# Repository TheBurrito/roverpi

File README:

RoPi - Robotics for the Raspberry Pi
https://github.com/TheBurrito/ropi

This repository contains all of the source code for both the Raspberry Pi and
the ATmega2560 on the RoPi expansion board.

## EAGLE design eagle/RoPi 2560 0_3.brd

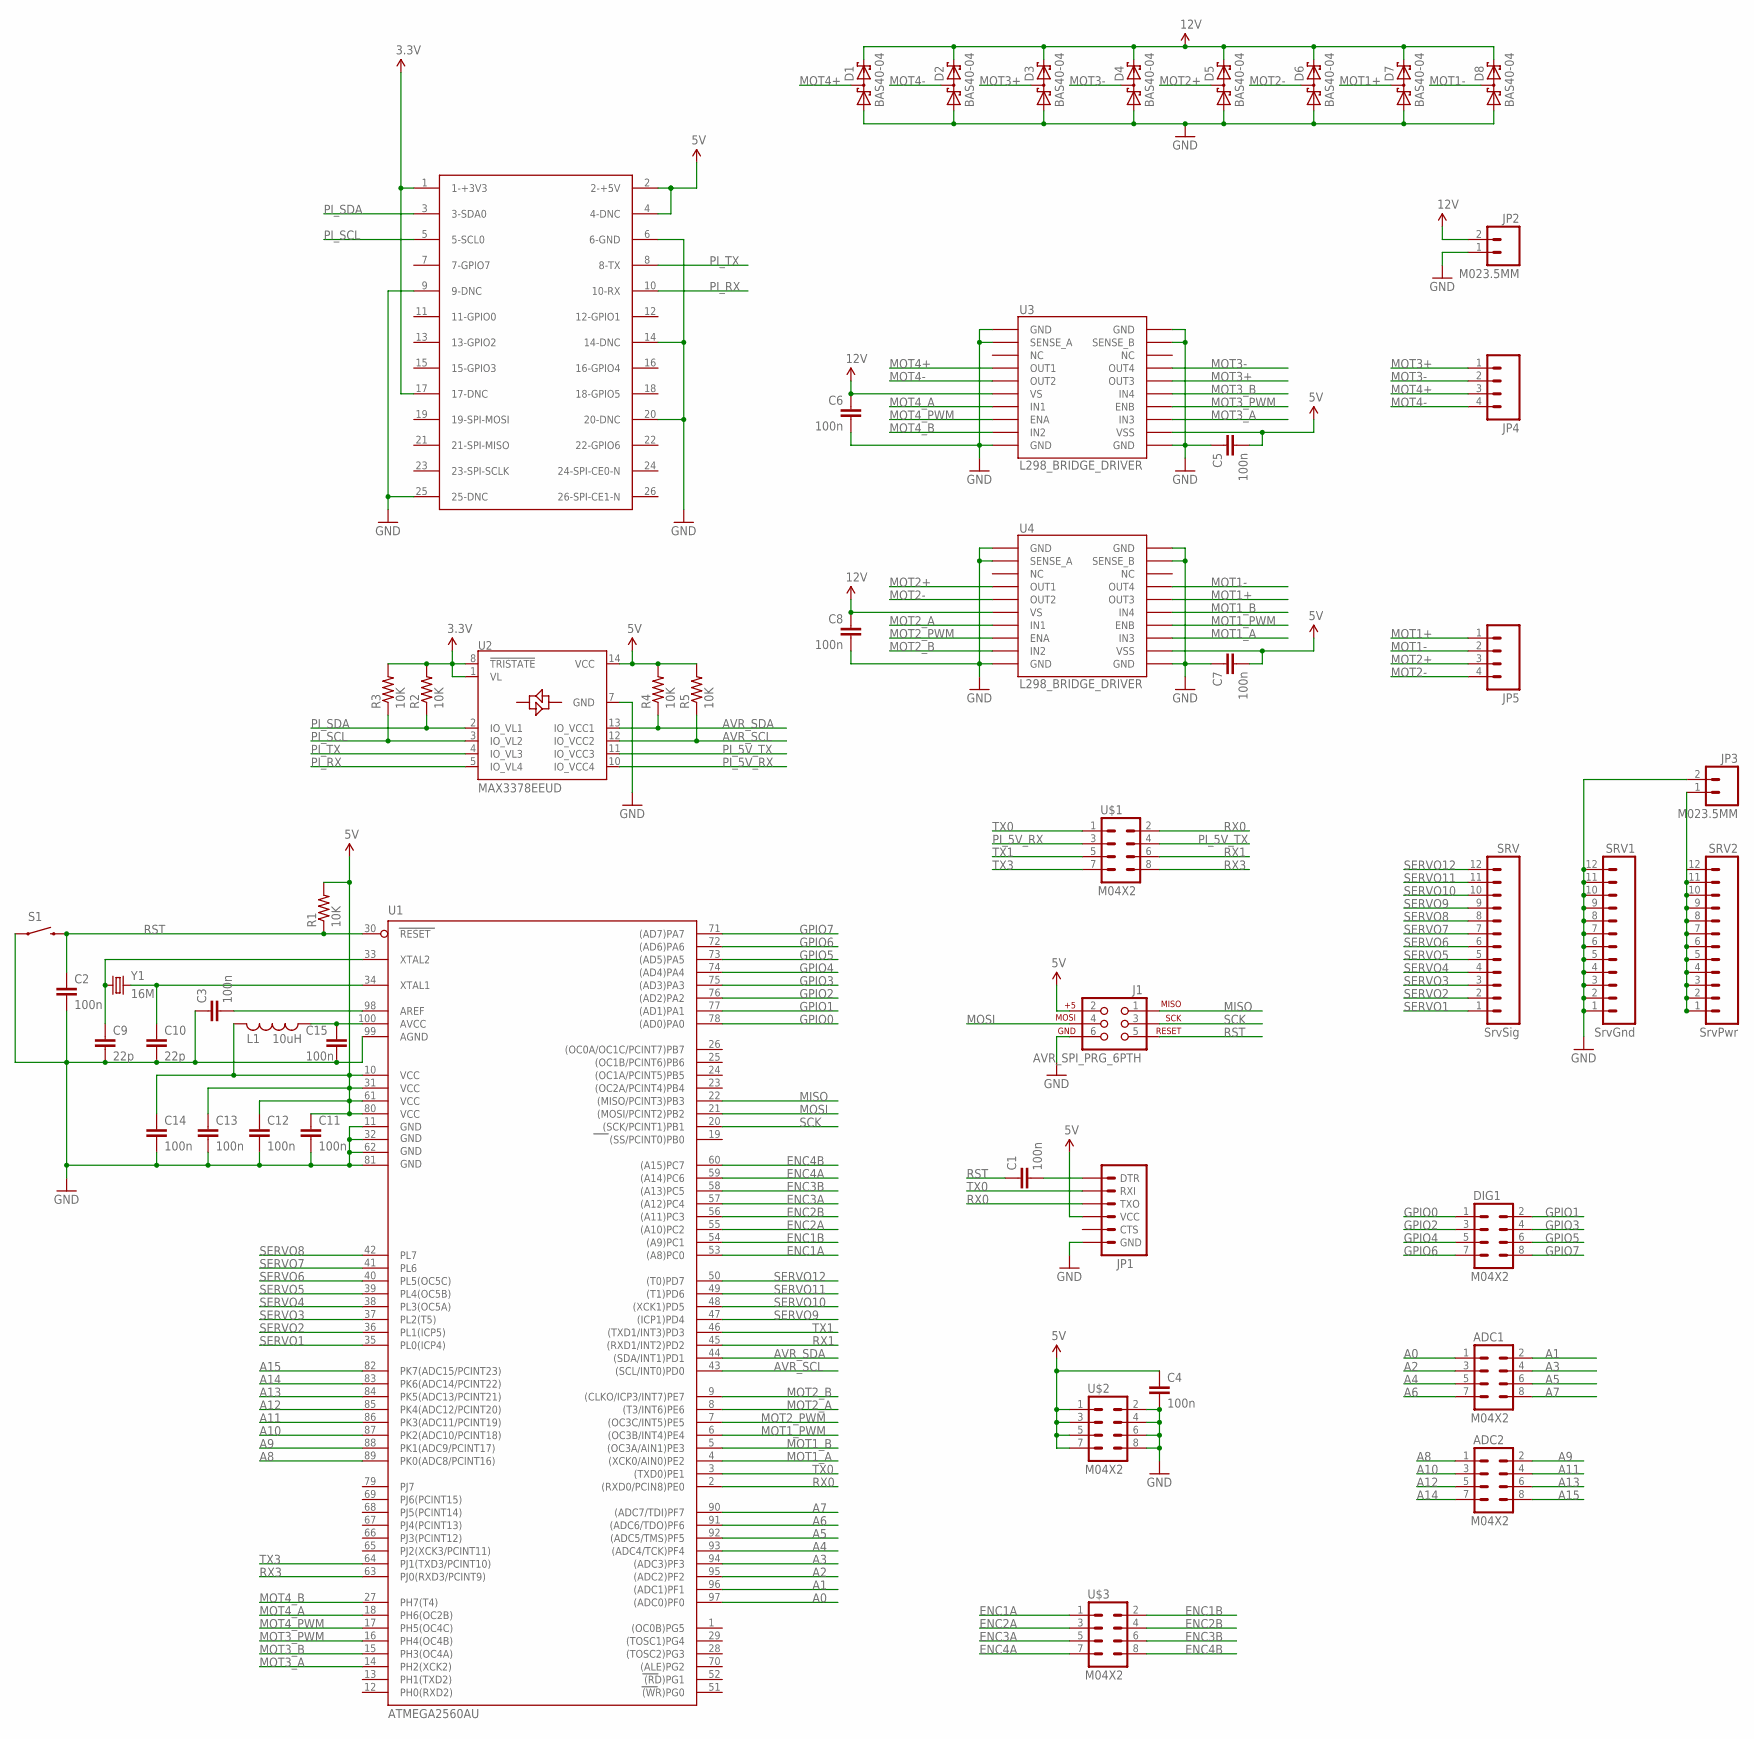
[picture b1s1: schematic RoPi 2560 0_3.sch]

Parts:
ADC1, ADC2: M04X2; 2X4
C1, C2, C3, C4, C5, C6, C7, C8, C11, C12, C13, C14, C15: 100n; 0603-CAP
C9, C10: 22p; 0603-CAP
D1, D2, D3, D4, D5, D6, D7, D8: BAS40-04; SOT23
DIG1: M04X2; 2X4
J1: AVR_SPI_PRG_6PTH; 2X3
JP1: ARDUINO_SERIAL_PROGRAMSMD; 1X06-SMD
JP2, JP3: M023.5MM; SCREWTERMINAL-3.5MM-2
JP4, JP5: M04SCREW; SCREWTERMINAL-3.5MM-4
L1: 10uH; R0603
PI: RASPBERRY-PI
R1, R2, R3, R4, R5: 10K; 0603-RES
S1: SWITCH-MOMENTARY-2SMD-4; TACTILE_SWITCH_TALL
SRV: SrvSig; 1X12
SRV1: SrvGnd; 1X12
SRV2: SrvPwr; 1X12
U1: ATMEGA2560AU; TQFP100
U2: MAX3378EEUD; TSSOP14
U3, U4: L298_BRIDGE_DRIVER; POWERSO20
U$1, U$2, U$3: M04X2; 2X4
Y1: 16M; HC49UP

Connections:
3.3V: PI.1 (1-+3V3), PI.17 (17-DNC), R2.2, R3.2, U2.1 (VL), U2.8 (!TRISTATE)
5V: C4.1, C5.2, C7.2, C11.1, C12.1, C13.1, C14.1, J1.2, JP1.4 (VCC), L1.2, PI.2 (2-+5V), PI.4 (4-DNC), R1.2, R4.2, R5.2, U1.10 (VCC), U1.31 (VCC1), U1.61 (VCC2), U1.80 (VCC3), U2.14 (VCC), U3.12 (VSS), U4.12 (VSS), U$2.1, U$2.3, U$2.5, U$2.7
A0: ADC1.1, U1.97 ((ADC0)PF0)
A1: ADC1.2, U1.96 ((ADC1)PF1)
A2: ADC1.3, U1.95 ((ADC2)PF2)
A3: ADC1.4, U1.94 ((ADC3)PF3)
A4: ADC1.5, U1.93 ((ADC4/TCK)PF4)
A5: ADC1.6, U1.92 ((ADC5/TMS)PF5)
A6: ADC1.7, U1.91 ((ADC6/TDO)PF6)
A7: ADC1.8, U1.90 ((ADC7/TDI)PF7)
A8: ADC2.1, U1.89 (PK0(ADC8/PCINT16))
A9: ADC2.2, U1.88 (PK1(ADC9/PCINT17))
A10: ADC2.3, U1.87 (PK2(ADC10/PCINT18))
A11: ADC2.4, U1.86 (PK3(ADC11/PCINT19))
A12: ADC2.5, U1.85 (PK4(ADC12/PCINT20))
A13: ADC2.6, U1.84 (PK5(ADC13/PCINT21))
A14: ADC2.7, U1.83 (PK6(ADC14/PCINT22))
A15: ADC2.8, U1.82 (PK7(ADC15/PCINT23))
AREF: C3.2, U1.98 (AREF)
AVR_SCL: R5.1, U1.43 ((SCL/INT0)PD0), U2.12 (IO_VCC2)
AVR_SDA: R4.1, U1.44 ((SDA/INT1)PD1), U2.13 (IO_VCC1)
DTR: C1.2, JP1.1 (DTR)
ENC1A: U1.53 ((A8)PC0), U$3.1
ENC1B: U1.54 ((A9)PC1), U$3.2
ENC2A: U1.55 ((A10)PC2), U$3.3
ENC2B: U1.56 ((A11)PC3), U$3.4
ENC3A: U1.57 ((A12)PC4), U$3.5
ENC3B: U1.58 ((A13)PC5), U$3.6
ENC4A: U1.59 ((A14)PC6), U$3.7
ENC4B: U1.60 ((A15)PC7), U$3.8
GND: C2.2, C3.1, C4.2, C5.1, C6.2, C7.1, C8.2, C9.2, C10.2, C11.2, C12.2, C13.2, C14.2, C15.2, D1.1 (A1), D2.1 (A1), D3.1 (A1), D4.1 (A1), D5.1 (A1), D6.1 (A1), D7.1 (A1), D8.1 (A1), J1.6, JP1.6 (GND), JP2.1, JP3.2, PI.6 (6-GND), PI.9 (9-DNC), PI.14 (14-DNC), PI.20 (20-DNC), PI.25 (25-DNC), S1.A2 (1), SRV1.1, SRV1.2, SRV1.3, SRV1.4, SRV1.5, SRV1.6, SRV1.7, SRV1.8, SRV1.9, SRV1.10, SRV1.11, SRV1.12, U1.11 (GND), U1.32 (GND1), U1.62 (GND2), U1.81 (GND3), U1.99 (AGND), U2.7 (GND), U3.1 (GND), U3.2 (SENSE_A), U3.10 (GND), U3.11 (GND), U3.19 (SENSE_B), U3.20 (GND), U4.1 (GND), U4.2 (SENSE_A), U4.10 (GND), U4.11 (GND), U4.19 (SENSE_B), U4.20 (GND), U$2.2, U$2.4, U$2.6, U$2.8
GPIO0: DIG1.1, U1.78 ((AD0)PA0)
GPIO1: DIG1.2, U1.77 ((AD1)PA1)
GPIO2: DIG1.3, U1.76 ((AD2)PA2)
GPIO3: DIG1.4, U1.75 ((AD3)PA3)
GPIO4: DIG1.5, U1.74 ((AD4)PA4)
GPIO5: DIG1.6, U1.73 ((AD5)PA5)
GPIO6: DIG1.7, U1.72 ((AD6)PA6)
GPIO7: DIG1.8, U1.71 ((AD7)PA7)
MISO: J1.1, U1.22 ((MISO/PCINT3)PB3)
MOSI: J1.4, U1.21 ((MOSI/PCINT2)PB2)
MOT1+: D7.3 (C1A2), JP5.1, U4.16 (OUT3)
MOT1-: D8.3 (C1A2), JP5.2, U4.17 (OUT4)
MOT1_A: U1.4 ((XCK0/AIN0)PE2), U4.13 (IN3)
MOT1_B: U1.5 ((OC3A/AIN1)PE3), U4.15 (IN4)
MOT1_PWM: U1.6 ((OC3B/INT4)PE4), U4.14 (ENB)
MOT2+: D5.3 (C1A2), JP5.3, U4.4 (OUT1)
MOT2-: D6.3 (C1A2), JP5.4, U4.5 (OUT2)
MOT2_A: U1.8 ((T3/INT6)PE6), U4.7 (IN1)
MOT2_B: U1.9 ((CLKO/ICP3/INT7)PE7), U4.9 (IN2)
MOT2_PWM: U1.7 ((OC3C/INT5)PE5), U4.8 (ENA)
MOT3+: D3.3 (C1A2), JP4.1, U3.16 (OUT3)
MOT3-: D4.3 (C1A2), JP4.2, U3.17 (OUT4)
MOT3_A: U1.14 (PH2(XCK2)), U3.13 (IN3)
MOT3_B: U1.15 (PH3(OC4A)), U3.15 (IN4)
MOT3_PWM: U1.16 (PH4(OC4B)), U3.14 (ENB)
MOT4+: D1.3 (C1A2), JP4.3, U3.4 (OUT1)
MOT4-: D2.3 (C1A2), JP4.4, U3.5 (OUT2)
MOT4_A: U1.18 (PH6(OC2B)), U3.7 (IN1)
MOT4_B: U1.27 (PH7(T4)), U3.9 (IN2)
MOT4_PWM: U1.17 (PH5(OC4C)), U3.8 (ENA)
unnamed: JP3.1, SRV2.1, SRV2.2, SRV2.3, SRV2.4, SRV2.5, SRV2.6, SRV2.7, SRV2.8, SRV2.9, SRV2.10, SRV2.11, SRV2.12
unnamed: C15.1, L1.1, U1.100 (AVCC)
PI_5V_RX: U2.10 (IO_VCC4), U$1.3
PI_5V_TX: U2.11 (IO_VCC3), U$1.4
PI_RX: PI.10 (10-RX), U2.5 (IO_VL4)
PI_SCL: PI.5 (5-SCL0), R3.1, U2.3 (IO_VL2)
PI_SDA: PI.3 (3-SDA0), R2.1, U2.2 (IO_VL1)
PI_TX: PI.8 (8-TX), U2.4 (IO_VL3)
RST: C1.1, C2.1, J1.5, R1.1, S1.B2 (2), U1.30 (RESET)
RX0: JP1.3 (TXO), U1.2 ((RXD0/PCIN8)PE0), U$1.2
RX1: U1.45 ((RXD1/INT2)PD2), U$1.6
RX3: U1.63 (PJ0(RXD3/PCINT9)), U$1.8
SCK: J1.3, U1.20 ((SCK/PCINT1)PB1)
SERVO1: SRV.1, U1.35 (PL0(ICP4))
SERVO2: SRV.2, U1.36 (PL1(ICP5))
SERVO3: SRV.3, U1.37 (PL2(T5))
SERVO4: SRV.4, U1.38 (PL3(OC5A))
SERVO5: SRV.5, U1.39 (PL4(OC5B))
SERVO6: SRV.6, U1.40 (PL5(OC5C))
SERVO7: SRV.7, U1.41 (PL6)
SERVO8: SRV.8, U1.42 (PL7)
SERVO9: SRV.9, U1.47 ((ICP1)PD4)
SERVO10: SRV.10, U1.48 ((XCK1)PD5)
SERVO11: SRV.11, U1.49 ((T1)PD6)
SERVO12: SRV.12, U1.50 ((T0)PD7)
TX0: JP1.2 (RXI), U1.3 ((TXD0)PE1), U$1.1
TX1: U1.46 ((TXD1/INT3)PD3), U$1.5
TX3: U1.64 (PJ1(TXD3/PCINT10)), U$1.7
V_BATT: C6.1, C8.1, D1.2 (C2), D2.2 (C2), D3.2 (C2), D4.2 (C2), D5.2 (C2), D6.2 (C2), D7.2 (C2), D8.2 (C2), JP2.2, U3.6 (VS), U4.6 (VS)
XTAL1: C10.1, U1.34 (XTAL1), Y1.2
XTAL2: C9.1, U1.33 (XTAL2), Y1.1

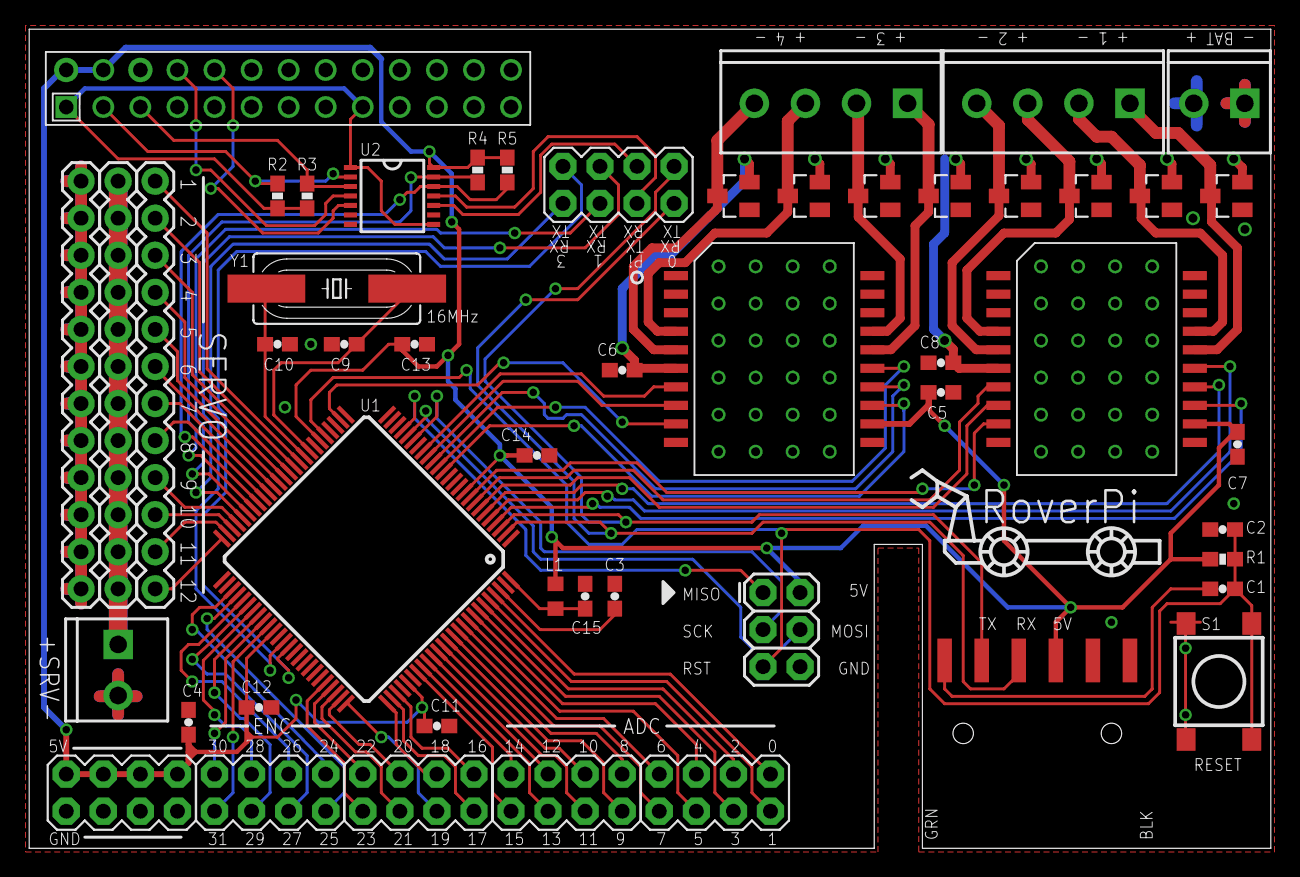
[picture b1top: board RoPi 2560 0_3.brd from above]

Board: 2 copper layers, 85.1 x 56.1 mm, 51 parts (0 on the bottom side), 92 nets.

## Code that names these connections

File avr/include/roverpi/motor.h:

/**

**/

#ifndef motor_h_
#define motor_h_

#include "base.h"
//#include <stdint.h>

#define DIV_OFF  0
#define DIV_1    1
#define DIV_8    2
#define DIV_64   3
#define DIV_256  4
#define DIV_1024 5

#ifndef MOTOR_PRESCALE
#define MOTOR_PRESCALE DIV_1
#endif

#ifndef MOTOR_FREQ
#define MOTOR_FREQ 10000
#endif

#if MOTOR_PRESCALE == DIV_1
#define MOTOR_N 1
#elif MOTOR_PRESCALE == DIV_8
#define MOTOR_N 8
#elif MOTOR_PRESCALE == DIV_64
#define MOTOR_N 64
#elif MOTOR_PRESCALE == DIV_256
#define MOTOR_N 256
#elif MOTOR_PRESCALE == DIV_1024
#define MOTOR_N 1024
#elif MOTOR_PRESCALE == DIV_OFF
#define MOTOR_N 0
#endif

#ifndef MOTOR_N
#error MOTOR_N could not be set. Ensure a proper value is set for MOTOR_PRESCALE
#define MOTOR_N 0
#endif

#if MOTOR_N == 0
#define MOTOR_TOP 0
#define MOTOR_TRUE_FREQ 0
#else
#define MOTOR_TOP ( F_CPU / (2 * MOTOR_N * MOTOR_FREQ) )
#define MOTOR_TRUE_FREQ ( F_CPU / (2 * MOTOR_N * MOTOR_TOP) )
#endif

#define MOTOR_TCCRnA 43
#define MOTOR_TCCRnB ( 16 | MOTOR_PRESCALE )

#define MOTOR1_PORT PORTE
#define MOTOR1_DDR DDRE
#define MOTOR1_PA PE2
#define MOTOR1_PB PE3
#define MOTOR1_PPWM PE4
#define MOTOR1_VAL OCR3B

#define MOTOR2_PORT PORTE
#define MOTOR2_DDR DDRE
#define MOTOR2_PA PE6
#define MOTOR2_PB PE7
#define MOTOR2_PPWM PE5
#define MOTOR2_VAL OCR3C

#define MOTOR3_PORT PORTH
#define MOTOR3_DDR DDRH
#define MOTOR3_PA PH2
#define MOTOR3_PB PH3
#define MOTOR3_PPWM PH4
#define MOTOR3_VAL OCR4B

#define MOTOR4_PORT PORTH
#define MOTOR4_DDR DDRH
#define MOTOR4_PA PH6
#define MOTOR4_PB PH7
#define MOTOR4_PPWM PH5
#define MOTOR4_VAL OCR4C

typedef enum {
	COAST,
	FORWARD,
	REVERSE,
	BRAKE
} MotorMode;

void motor_init();

void set_motor(uint8_t num, MotorMode mode, uint16_t val);

#endif

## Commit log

2014-03-13 Adding eagle files for RoPi expansion board
2014-03-13 Copying over buildsys updates from AVR folder.
2014-03-15 Removed 5V <-> 3V3 selector jumper as an ATmega2560 running at 16MHz can only be supplied 5V
2014-03-19 Leaving 2nd revision board as-is; will not be ordering 0.2 board.
    0.3 is a complete re-routing and layout adjustment. The ATmega has been
    moved closer to the bottom left corner. The slot for the camera cable has
    been adjusted to the left a bit to better sit squarely over the connector.
    The reset switch and passives have been moved over the ethernet connector
    adjacent to the FTDI header. The ISP header has also been moved away from
    the edge to allow a normal IDC connector to fit.
2014-04-08 Updated name to RoverPi, moved arduino library into /arduino/RoverPi
2014-04-08 Updated readme file
2014-04-08 Renamed remaining ropi folders to roverpi, gitignore files in output folders
2014-04-08 renamed another ropi folder

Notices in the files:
parts and their libraries:
SparkFun-DigitalIC: Licensing: Creative Commons ShareAlike 4.0 International - https://creativecommons.org/licenses/by-sa/4.0
